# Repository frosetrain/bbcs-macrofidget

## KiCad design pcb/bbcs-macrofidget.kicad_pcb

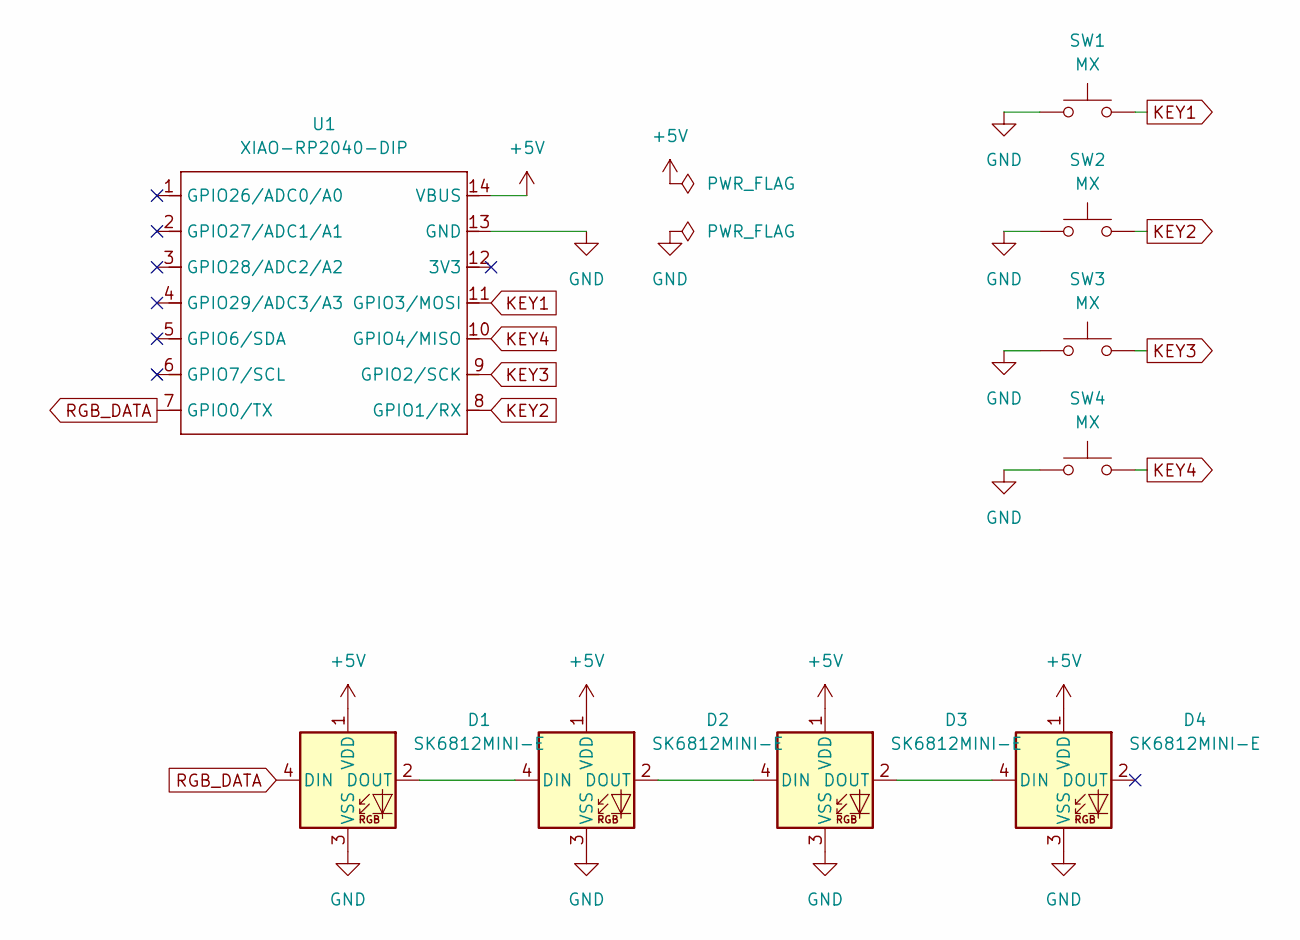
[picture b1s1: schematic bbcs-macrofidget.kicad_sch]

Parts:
D1, D2, D3, D4: SK6812MINI-E; MX_SK6812MINI-E_GOOD
SW1, SW2, SW3, SW4: MX; MX-Solderable-1U
U1: XIAO-RP2040-DIP; XIAO-RP2040-THT

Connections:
+5V: D1.1 (VDD), D2.1 (VDD), D3.1 (VDD), D4.1 (VDD), U1.14 (VBUS)
GND: D1.3 (VSS), D2.3 (VSS), D3.3 (VSS), D4.3 (VSS), SW1.1, SW2.1, SW3.1, SW4.1, U1.13 (GND)
KEY1: SW1.2, U1.11 (GPIO3/MOSI)
KEY2: SW2.2, U1.8 (GPIO1/RX)
KEY3: SW3.2, U1.9 (GPIO2/SCK)
KEY4: SW4.2, U1.10 (GPIO4/MISO)
unnamed: D1.2 (DOUT), D2.4 (DIN)
unnamed: D2.2 (DOUT), D3.4 (DIN)
unnamed: D3.2 (DOUT), D4.4 (DIN)
RGB_DATA: D1.4 (DIN), U1.7 (GPIO0/TX)

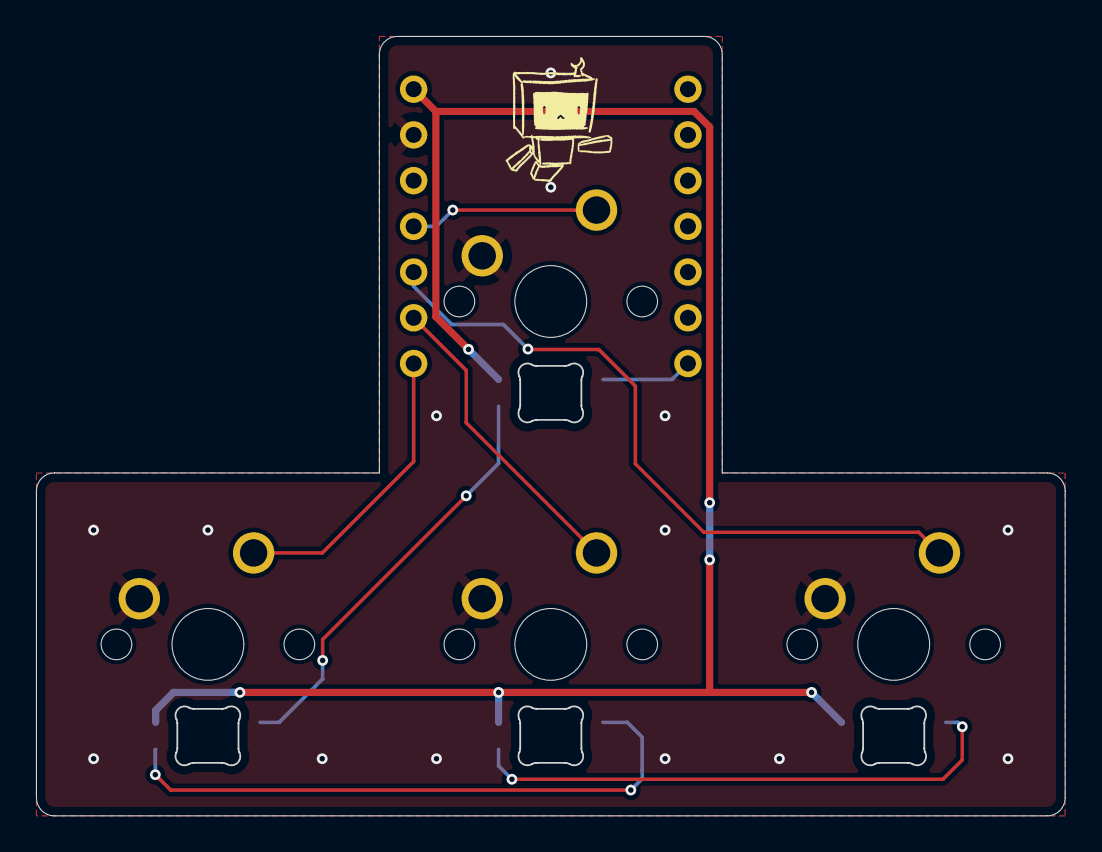
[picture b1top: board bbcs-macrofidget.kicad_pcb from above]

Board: 2 copper layers, 57.2 x 43.3 mm, 9 parts (1 on the bottom side), 10 nets.

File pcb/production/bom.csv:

Designator,Footprint,Quantity,Value,LCSC Part #
"D1, D2, D3, D4",MX_SK6812MINI-E_GOOD,4,SK6812MINI-E,
"SW1, SW2, SW3, SW4",MX-Solderable-1U,4,MX,
U1,XIAO-RP2040-THT,1,XIAO-RP2040-DIP,
